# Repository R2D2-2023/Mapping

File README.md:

# Mapping
Git repository voor de mapping groep (positie bepaling 1)

installeer ros-melodic-desktop-full git ros-melodic-cartographer-ros ros-melodic-gazebo-msgs ros-melodic-gazebos-plugins python-rosdep2 pycrypto libsdl1.2-dev libsdl-image1.2 libsdl-image1.2-dev

installeer op x86/x86_64 rosmelodic-desktop-full docker rosbridge_suite

```bash
source /opt/ros/melodic/setup.bash

git clone https://github.com/YDLIDAR/YDLidar-SDK
cd YDLidar-SDK
mkdir build
cmake ..
make
sudo make install
cd ~

mkdir ydlidar_ws
cd ydlidar_ws
git clone https://github.com/YDLIDAR/ydlidar_ros_driver src
catkin_make
catkin_make install
source devel/setup.bash
cd ~

mkdir gbot_core_ws
cd gbot_core_ws
https://github.com/JSaurusRex/gbot_core_ydlidar src
catkin_make
catkin_make install
source devel/setup.bash
cd ~

mkdir map_server
cd map_server
git clone https://github.com/ros-planning/navigation
mv navigation/map_server src
rm -rf navigation
catkin_make
catkin_make install
source devel/setup.bash
cd ~
```

#done with installation
#to run
```bash
ROS_IP=(ip of x86/x86_64) ROS_MASTER_URI=(ip of rosserver/machine) roslaunch gbot_core gbot.launch #starts cartographer
roslaunch gbot_core visualization.launch #for visualization (requires gui)
rosrun map_server map_saver #saves map

#for webserver
#on x86/x86_64
ROS_IP=(ip of rosserver) roslaunch rosbridge_server rosbridge_websocket.launch
docker run -p 8080:8080 cruise/webviz
```
(ip of x86/x86_64):8080/?rosbridge-websocket-url=ws://(ip of rosserver)

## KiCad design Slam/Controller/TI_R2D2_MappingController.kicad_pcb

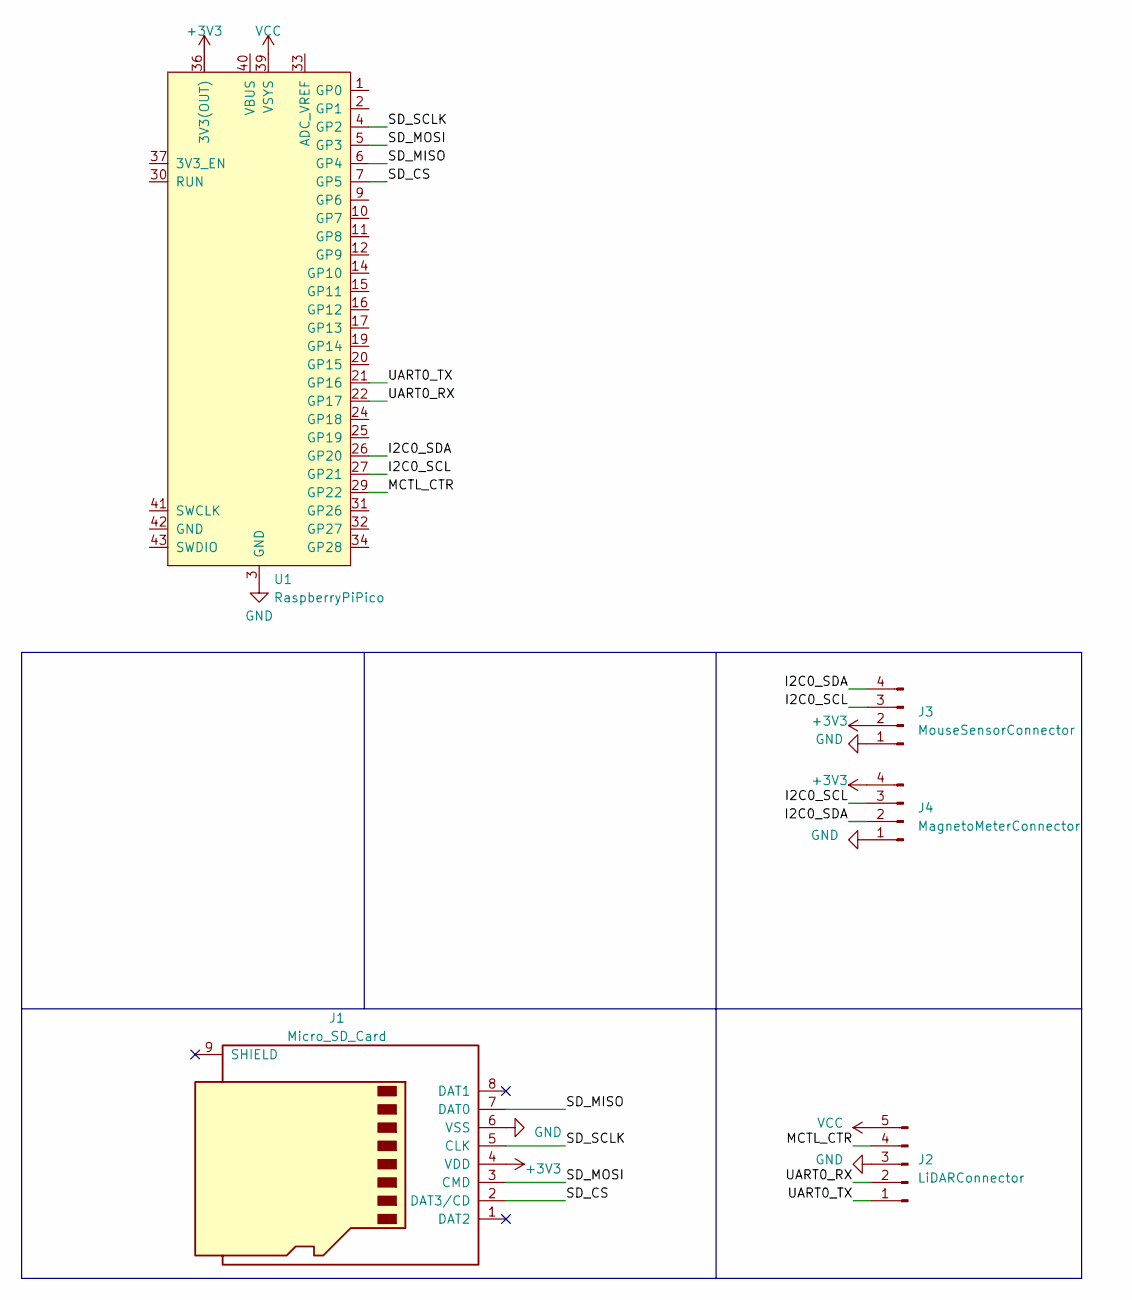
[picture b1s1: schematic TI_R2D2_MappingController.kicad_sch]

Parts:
J1: Micro_SD_Card; microSD_HC_Molex_104031-0811
J2: LiDARConnector; PinSocket_1x05_P2.54mm_Vertical
J3: MouseSensorConnector; PinSocket_1x04_P2.54mm_Vertical
J4: MagnetoMeterConnector; PinSocket_1x04_P2.54mm_Vertical
U1: RaspberryPiPico; RPi_Pico

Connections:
+3V3: J1.4 (VDD), J3.2, J4.4, U1.36 (3V3(OUT))
/I2C0_SCL: J3.3, J4.3, U1.27 (GP21)
/I2C0_SDA: J3.4, J4.2, U1.26 (GP20)
/MCTL_CTR: J2.4, U1.29 (GP22)
/SD_CS: J1.2 (DAT3/CD), U1.7 (GP5)
/SD_MISO: J1.7 (DAT0), U1.6 (GP4)
/SD_MOSI: J1.3 (CMD), U1.5 (GP3)
/SD_SCLK: J1.5 (CLK), U1.4 (GP2)
/UART0_RX: J2.2, U1.22 (GP17)
/UART0_TX: J2.1, U1.21 (GP16)
GND: J1.6 (VSS), J2.3, J3.1, J4.1, U1.3 (GND), U1.8 (GND), U1.13 (GND), U1.18 (GND), U1.23 (GND), U1.28 (GND), U1.33 (GND), U1.38 (GND)
VCC: J2.5, U1.39 (VSYS)

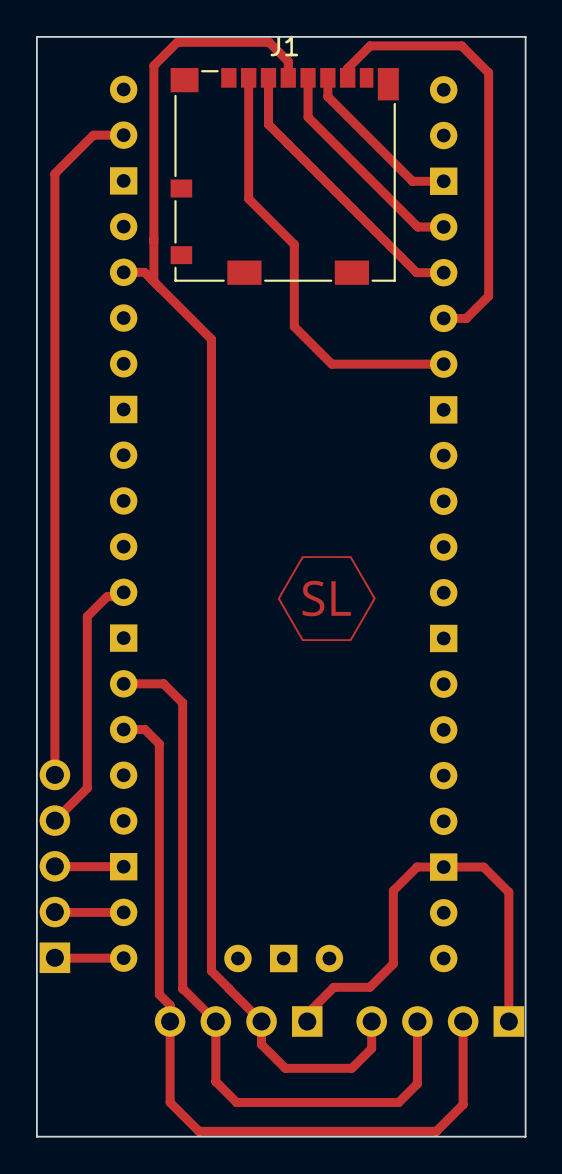
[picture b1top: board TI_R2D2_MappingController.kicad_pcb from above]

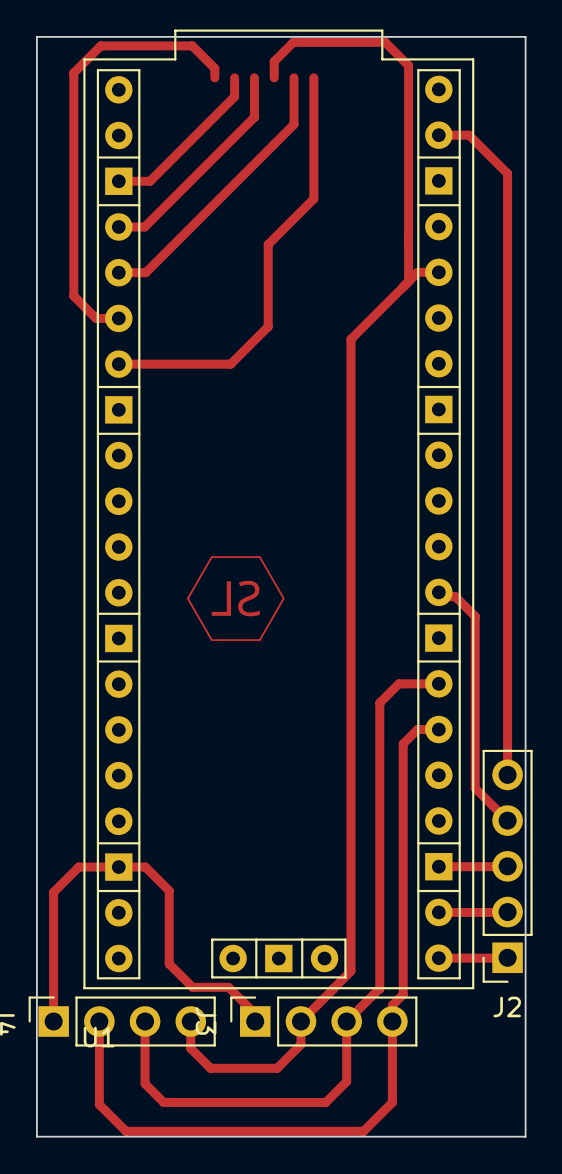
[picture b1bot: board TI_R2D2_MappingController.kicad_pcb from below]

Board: 2 copper layers, 27.1 x 61.1 mm, 5 parts (4 on the bottom side), 12 nets.

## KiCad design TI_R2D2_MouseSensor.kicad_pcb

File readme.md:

# Mapping
This repository contains code in Python and C++ that allows you to create a grid from a given image, draw on it, and save the drawn values. Additionally, the Python code includes functionality to read the saved route and visualize it. The code utilizes the OpenCV library for image processing and manipulation.

## Prerequisites
- Python 3.9.x or higher
- C++ compiler
- [OpenCV library](https://opencv.org/)

## Hardware
- [YDLidar x2](https://www.ydlidar.com/products/view/6.html) or better
- [raspberry pi 4](https://www.raspberrypi.com/products/raspberry-pi-4-model-b/)
- [rc car](https://www.toprc.nl/rc-autos/)

## installation
1. Clone the repository:
- git clone https://github.com/R2D2-2023/Mapping.git
- Alternatively, you can download the repository as a ZIP file and extract it.

2. Navigate to the "Ros" directory and follow the instructions in the [README](Ros/README.md) file to download and set up the required dependencies for the Lidar-based mapping module.

## Usage

### Python Code

1. Install the necessary Python packages:
- pip install -r /path/to/requirements.txt [requirements](make_grid/make_grid_Python/requirements.txt)
2. Run the Python script in [main.py](make_grid/make_grid_Python/main.py) to generate a grid from an image and draw on it
3. Save the drawn values on closing the program
4. run [read.py](make_grid/make_grid_Python//read.py) to visualize the saved route
- The script will display the input image with the drawn route highlighted.

### C++ Code
1. Compile the C++ code in [main.cpp](make_grid/make_grid_C%2B%2B/main.cpp) using your preferred compiler. Make sure OpenCV is properly installed and linked and use this command to compile:
```
  g++ -g main.cpp -o main -I C:\OpenCV-MinGW-Build-OpenCV-4.1.1-x64\include -L C:\OpenCV-MinGW-Build-OpenCV-4.1.1-x64\x64\mingw\bin -llibopencv_calib3d411 -llibopencv_core411 -llibopencv_dnn411 -llibopencv_features2d411 -llibopencv_flann411 -llibopencv_highgui411 -llibopencv_imgcodecs411 -llibopencv_imgproc411 -llibopencv_ml411 -llibopencv_objdetect411 -llibopencv_photo411 -llibopencv_stitching411 -llibopencv_video411 -llibopencv_videoio411
```

2. Run the compiled executable.
The program will display the image with a grid overlaid on it. use your mouse to draw and the scroll wheel to change the drawing modes.
3. Save the drawn values by closing the program

## Lidar-based Mapping (Ros)
For the Lidar-based mapping module, please refer to the [Ros](Ros) directory for detailed instructions on how to download and use it.

## Authors
- [@BasvandenBergh](https://github.com/BasvandenBergh)
- [@jamesonLin](https://www.github.com/jamesonLin)
- [@Jorismaas](https://github.com/Jorismaas)
- [@JSaurusRex](https://github.com/JSaurusRex)
- [@LukkenS-HU](https://github.com/LukkenS-HU)

## Contributors
- [@northernlakeNL](https://github.com/northernlakeNL)

## License

## Acknowledgements
- [OpenCV](https://opencv.org/) - Open Source Computer Vision Library
- [cartographer](https://github.com/cartographer-project/cartographer)  - Open Source Lidar Library

Please refer to the individual code files for specific attributions and licenses.

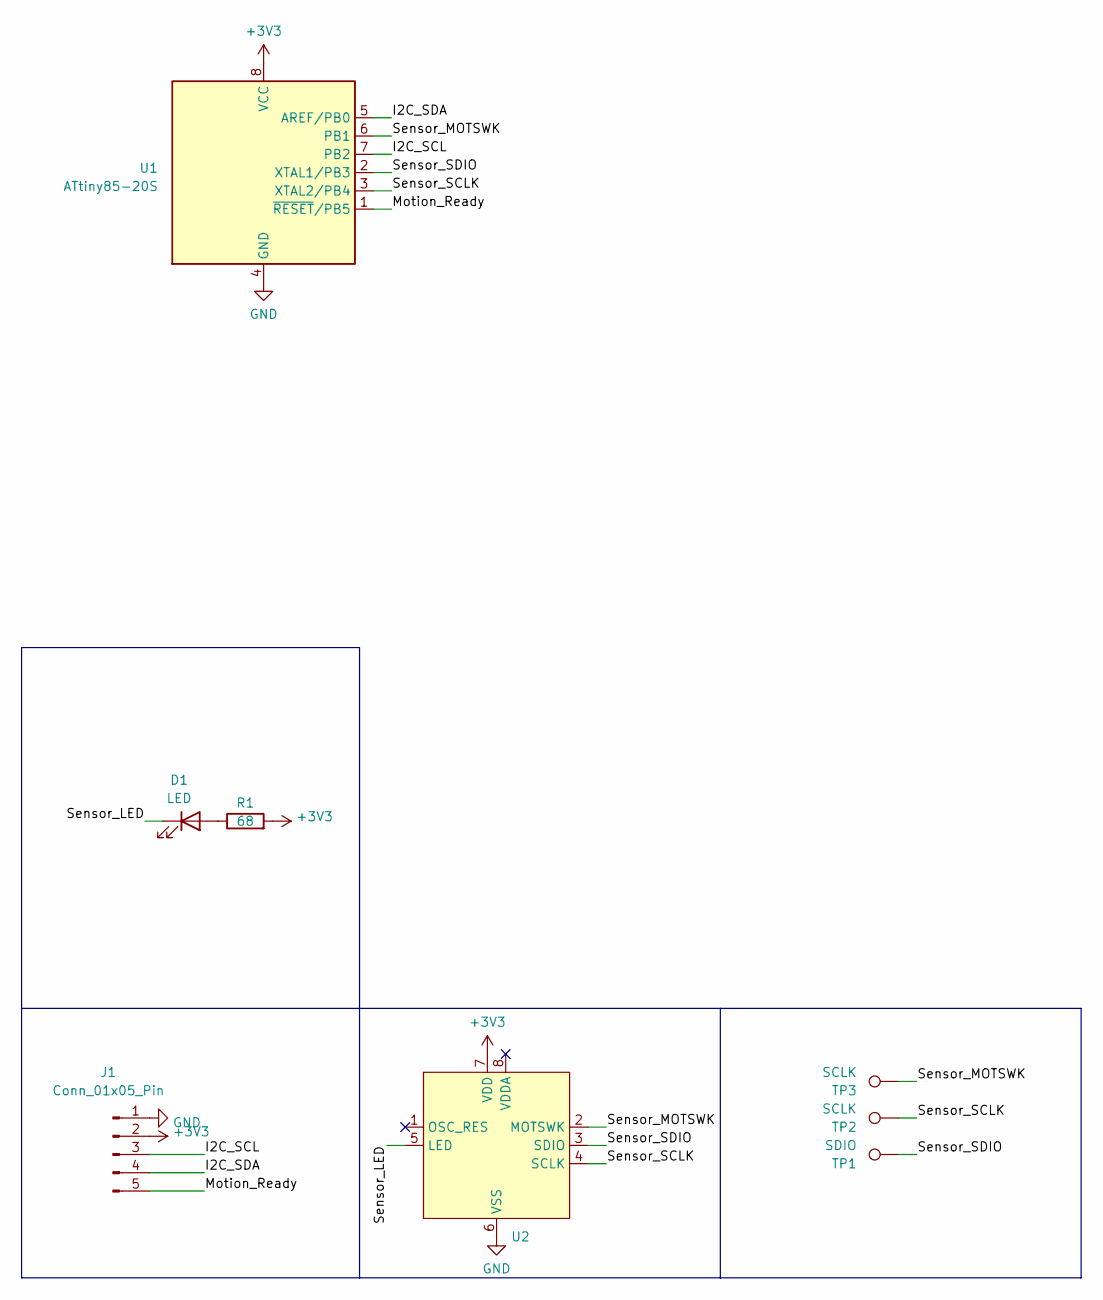
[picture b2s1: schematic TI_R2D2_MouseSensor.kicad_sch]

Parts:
D1: LED; LED_D5.0mm
J1: Conn_01x05_Pin; PinHeader_1x05_P2.54mm_Vertical
R1: 68; R_0805_2012Metric
TP1: SDIO; TestPoint_Pad_D1.5mm
TP2, TP3: SCLK; TestPoint_Pad_D1.5mm
U1: ATtiny85-20S; SOIC-8W_5.3x5.3mm_P1.27mm
U2: FCT-3065

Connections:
+3V3: J1.2, R1.2, U1.8 (VCC), U2.7 (VDD)
/I2C_SCL: J1.3, U1.7 (PB2)
/I2C_SDA: J1.4, U1.5 (AREF/PB0)
/Motion_Ready: J1.5, U1.1 (~RESET/PB5)
/Sensor_LED: D1.1 (K), U2.5 (LED)
/Sensor_MOTSWK: TP3.1, U1.6 (PB1), U2.2 (MOTSWK)
/Sensor_SCLK: TP2.1, U1.3 (XTAL2/PB4), U2.4 (SCLK)
/Sensor_SDIO: TP1.1, U1.2 (XTAL1/PB3), U2.3 (SDIO)
GND: J1.1, U1.4 (GND), U2.6 (VSS)
unnamed: D1.2 (A), R1.1

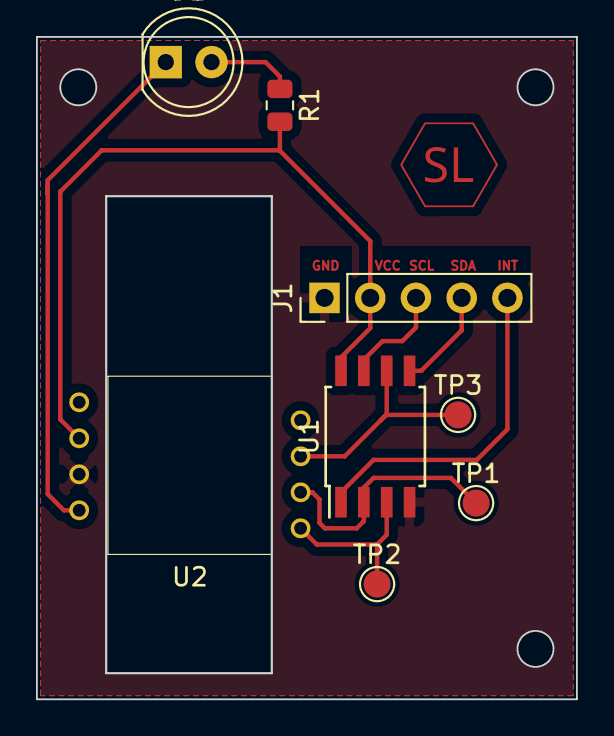
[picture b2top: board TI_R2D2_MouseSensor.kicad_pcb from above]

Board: 2 copper layers, 30.0 x 36.8 mm, 8 parts (0 on the bottom side), 10 nets.

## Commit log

2023-03-31 Added QR-code scan for windows
2023-03-31 Added QR-code creator
2023-03-31 Added QR-code scan for Linux
2023-04-05 Added gitignore
2023-04-11 draw line on image grid
    changes images to images with a visual and virtual grid
    laat je een lijn tekenen binnen deze grid die vervolgens zichtbaar wordt visueel, maar ook virtueel
2023-04-11 updated the code, updates the image per change
2023-04-11 updated the code, removes line on grid
2023-04-12 inital jesse branch commit
2023-04-12 updated readme to have description of folder
2023-04-12 added manual scans
2023-04-12 Updated readme with little explonation / description for scans
2023-04-12 Add some images of the finished PCB
2023-04-12 Add LICENSE
2023-04-12 Update images & add Case image
2023-04-13 Added doxygen in code
2023-04-13 Added doxygen generated pages
2023-04-13 magnetometer raw data
    geeft rauwe data van LSM303
2023-04-13 calibration tool
    calibrates before sending data
2023-04-13 Added gitignore and QR-Code images
2023-04-13 Added doxygen
2023-04-13 Add image of Case
2023-05-24 Update main.cpp
    added functions to find the next grid to move to using the robots position and checking the surrounding tiles for the highest number nearby that isnt 0
2023-06-20 Added code from Joris
2023-06-20 included setup instructions for installation ros / cartographer that @LukkenS-HU and i use
2023-06-20 included setup instructions for installation ros / cartographer
2023-06-23 Bas het fixen dat de foto op elk scherm op de zelfde resulutie eruit komt
2023-06-23 improved the oneMouse and windows scaling, met Joris en bas
2023-06-23 fixed onMouse, it works again, met Joris en Bas
2023-06-23 eerste poging c++ naar python voor de grid tom bas en jameson
2023-06-23 bas debug aan double aan roepen van window
2023-06-26 Update README.md met hoe webserver op te zetten
2023-06-26 een nieuw bestand met een leeg grid om later de text file uit te lezen
2023-06-27 new map met corner gridspots die een andere kleur krijgen dan de andere grid spots
2023-06-27 new map
2023-06-27 new map vergeten in read.py te zetten
2023-06-27 Delete Toerk_map.png
    oude map lokaal verwijderd en dat gebeurde remote niet
2023-06-28 beste route opgeslagen en minor updates
2023-06-28 added new map
2023-06-29 added function for pixel coords to grid coords
2023-07-04 mappen structuur aangepast
2023-07-04 mappen stuctuur en rewadme toegevoegd
2023-07-04 OpenCV-MinGW-Build-OpenCV-4.1.1-x641.zip toeggevoegd
2023-07-04 readme aangepast
2023-07-04 readme verplaatst
2023-07-04 added all made maps
2023-07-04 changed map structure
2023-07-04 deleted not used information
2023-07-04 update doxygen and readme
2023-07-04 updated readme and added requirements.txt
2023-07-04 updated readme and doxygen output
2023-07-04 updated readme added Contributors
2023-07-04 updated code style and doxygen
2023-07-04 updated readme and license

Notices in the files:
readme.md:
License:
[MIT License](https://choosealicense.com/licenses/mit/)
